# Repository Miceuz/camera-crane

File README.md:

# camera-crane
Electronics of camera crane for stop motion animation

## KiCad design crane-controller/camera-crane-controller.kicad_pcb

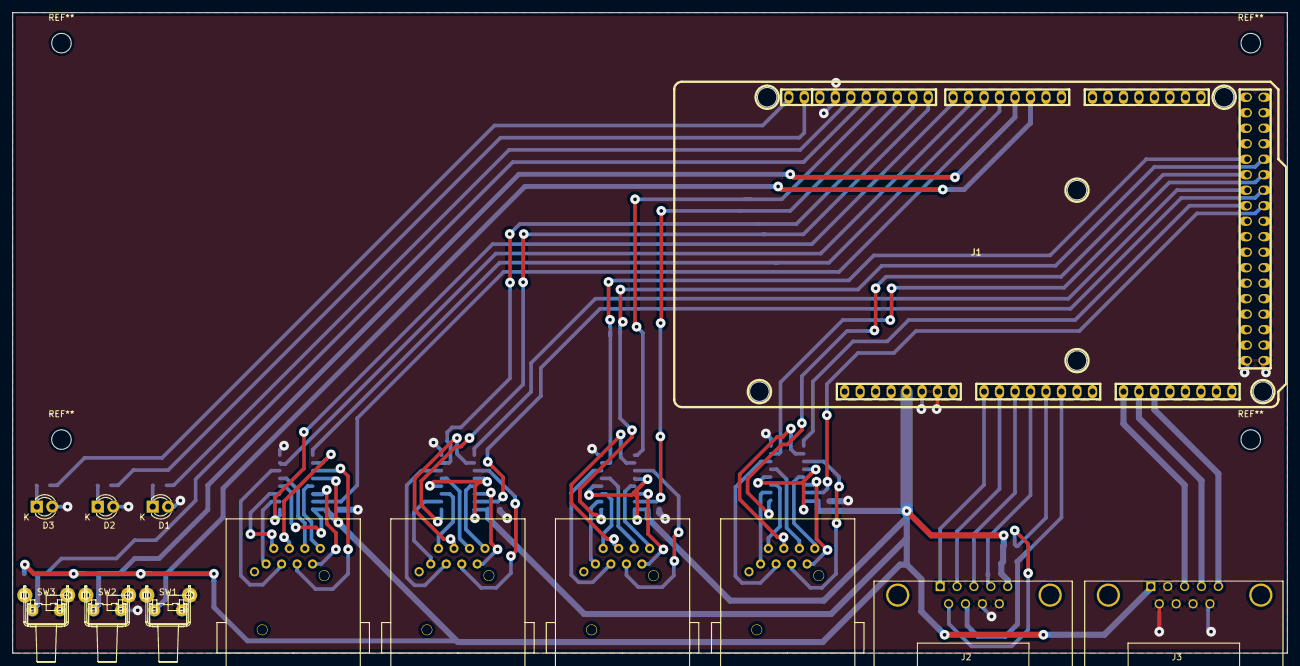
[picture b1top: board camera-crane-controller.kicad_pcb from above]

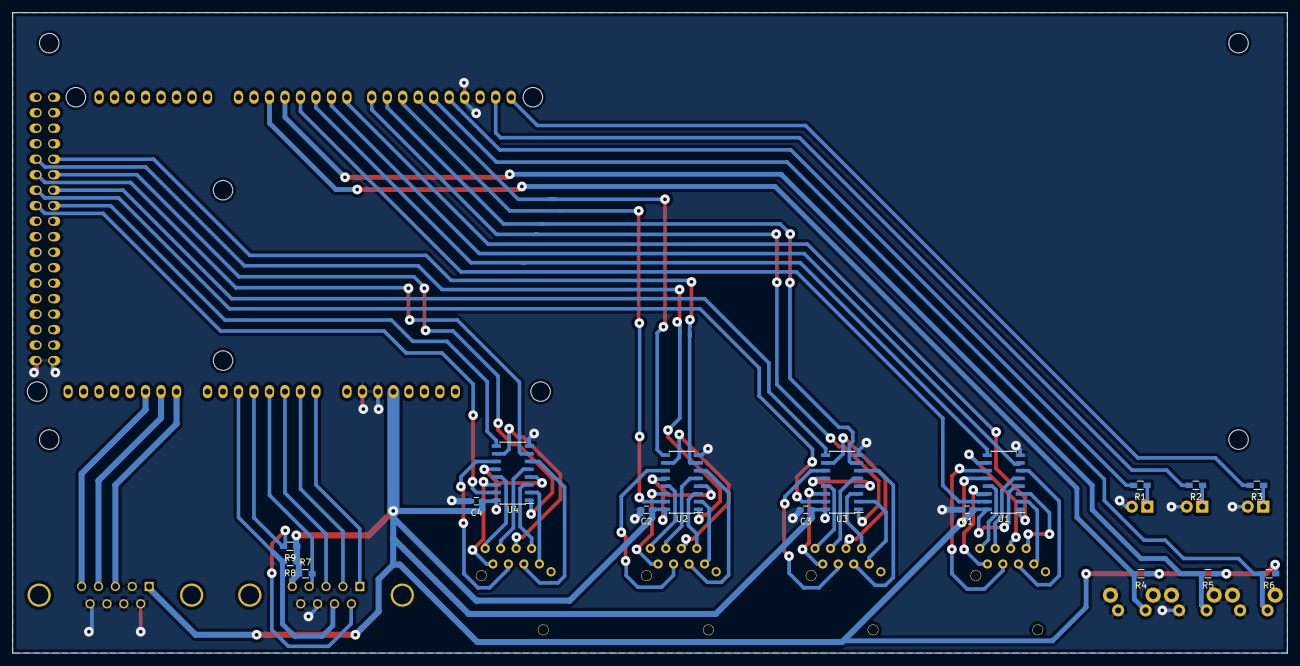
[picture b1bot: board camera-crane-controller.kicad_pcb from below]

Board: 2 copper layers, 209.0 x 105.0 mm, 30 parts (17 on the bottom side), 68 nets.

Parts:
C1, C2, C3, C4: C; C_0603_HandSoldering
D1, D2, D3: LED; LED-3MM
J1: Arduino_Mega_Header; arduino_mega_header
J2: DB9; 182-009-113
J3: DB9; DB9MC
P1, P2, P3, P4: CONN_01X08; NE8FAH
R1, R2, R3, R4, R5, R6: R; R_0603_HandSoldering
R7, R8, R9: 1k; R_0603_HandSoldering
SW1, SW2, SW3: SW_PUSH; SKHHLR
U1, U2, U3, U4: MAX3040; SOIC-16_3.9x9.9mm_Pitch1.27mm

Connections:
/DIR_AUX1: J1.54, U3.15
/DIR_AUX2: J1.53, U4.15
/DIR_FOCUS: J1.55, U4.7
/DIR_PAN: J1.80, U2.9
/DIR_TILT: J1.56, U2.1
/DIR_X: J1.74, U1.9
/DIR_Y: J1.76, U1.1
/DIR_Z: J1.78, U3.7
/END_SW1: J1.17, J3.3
/END_SW2: J1.18, J3.4
/END_SW3: J1.19, J3.5
/JOY_BUTTON_BOT: J1.13, J2.6, R9.2
/JOY_BUTTON_DEADMAN: J1.12, J2.4, R7.2
/JOY_BUTTON_TOP: J1.14, J2.7, R8.2
/JOY_REF: J1.9, J2.1
/JOY_X: J1.10, J2.2
/JOY_Y: J1.11, J2.3
/LED1: J1.82, R1.2
/LED2: J1.85, R2.2
/LED3: J1.86, R3.2
/STEP_AUX1: J1.36, U3.9
/STEP_AUX2: J1.35, U4.9
/STEP_FOCUS: J1.37, U4.1
/STEP_PAN: J1.79, U2.15
/STEP_TILT: J1.38, U2.7
/STEP_X: J1.73, U1.15
/STEP_Y: J1.75, U1.7
/STEP_Z: J1.77, U3.1
/SW1: J1.71, R4.2, SW1.1
/SW2: J1.72, R5.2, SW2.1
/SW3: J1.81, R6.2, SW3.1
GND: C1.2, C2.2, C3.2, C4.2, D1.2, D2.2, D3.2, J1.6, J1.7, J1.25, J1.43, J1.83, J2.8, J2.9, J3.2, J3.6, J3.7, J3.8, J3.9, SW1.2, SW1.G, SW2.2, SW2.G, SW3.2, SW3.G, U1.8, U2.8, U3.8, U4.8
unnamed: D1.1, R1.1
unnamed: D2.1, R2.1
unnamed: D3.1, R3.1
unnamed: P1.1, U1.2
unnamed: P1.2, U1.3
unnamed: P1.3, U1.6
unnamed: P1.4, U1.10
unnamed: P1.5, U1.11
unnamed: P1.6, U1.5
unnamed: P1.7, U1.14
unnamed: P1.8, U1.13
unnamed: P2.1, U3.2
unnamed: P2.2, U3.3
unnamed: P2.3, U3.6
unnamed: P2.4, U3.10
unnamed: P2.5, U3.11
unnamed: P2.6, U3.5
unnamed: P2.7, U3.14
unnamed: P2.8, U3.13
unnamed: P3.1, U2.2
unnamed: P3.2, U2.3
unnamed: P3.3, U2.6
unnamed: P3.4, U2.10
unnamed: P3.5, U2.11
unnamed: P3.6, U2.5
unnamed: P3.7, U2.14
unnamed: P3.8, U2.13
unnamed: P4.1, U4.2
unnamed: P4.2, U4.3
unnamed: P4.3, U4.6
unnamed: P4.4, U4.10
unnamed: P4.5, U4.11
unnamed: P4.6, U4.5
unnamed: P4.7, U4.14
unnamed: P4.8, U4.13
VCC: C1.1, C2.1, C3.1, C4.1, J1.5, J1.42, J1.60, J2.5, J3.1, R4.1, R5.1, R6.1, R7.1, R8.1, R9.1, U1.4, U1.12, U1.16, U2.4, U2.12, U2.16, U3.4, U3.12, U3.16, U4.4, U4.12, U4.16

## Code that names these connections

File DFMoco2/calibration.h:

#include "common.h"
#include <Bounce2.h>

#define baseForward()     digitalWrite(DIR_BASE, LOW)
#define baseReverse()     digitalWrite(DIR_BASE, HIGH)
#define panForward()      digitalWrite(DIR_PAN, HIGH)
#define panReverse()      digitalWrite(DIR_PAN, LOW)
#define tiltForward()      digitalWrite(DIR_TILT, HIGH)
#define tiltReverse()      digitalWrite(DIR_TILT, LOW)

#define LED1 13
#define LED2 20
#define LED3 21

#define SW1 2
#define SW2 3
#define SW3 12

#define END_SW1 A8
#define END_SW2 A9
#define END_SW3 A10

Bounce sw1 = Bounce(SW1, 10);
Bounce sw2 = Bounce(SW2, 10);
Bounce sw3 = Bounce(SW3, 10);

Bounce esw1 = Bounce(END_SW1, 10);
Bounce esw2 = Bounce(END_SW2, 10);
Bounce esw3 = Bounce(END_SW3, 10);

uint32_t stepTs;
uint16_t pulseUs = 4000;

uint32_t steps = 0;
uint8_t phase = HIGH;

void calibrateSetup() {
  pinMode(LED1, OUTPUT);
  pinMode(LED2, OUTPUT);
  pinMode(LED3, OUTPUT);

  digitalWrite(LED1, HIGH);
  digitalWrite(LED2, HIGH);
  digitalWrite(LED3, HIGH);
  delay(2000);
  digitalWrite(LED1, LOW);
  digitalWrite(LED2, LOW);
  digitalWrite(LED3, LOW);
}

void move(uint8_t stepPin, uint32_t stepsToDo, uint8_t waitForSwitch) {
  steps = 0;
  while(steps < stepsToDo) {
    if(isPulseTime(stepTs, pulseUs)) {
      digitalWrite(stepPin, phase);
      phase = !phase;
      steps++;
      stepTs = micros();

      esw1.update();
      esw2.update();
      esw3.update();

      if(esw1.read()) {
        if(waitForSwitch && STEP_BASE == stepPin) {
          break;
        }
      }

      if(esw2.read()) {
        if(waitForSwitch && STEP_PAN == stepPin) {
          break;
        }
      }

      if(esw3.read()) {
        if(waitForSwitch && STEP_TILT == stepPin) {
          break;
        }
      }
    }
  }
  Serial.println(String("Done ") + steps + String(" out of ") + stepsToDo);
}

uint8_t touchBase() {
  digitalWrite(LED3, LOW);
  digitalWrite(LED2, HIGH);

  pulseUs = 500;
  baseForward();
  move(STEP_BASE, 10000, 1);
  if(steps == 10000) {
    digitalWrite(LED3, HIGH);
    return 0;
  }
  delay(2000);

  pulseUs = 1000;
  baseReverse();
  move(STEP_BASE, 1000, 0);

  delay(2000);
  
  pulseUs = 8000;
  baseForward();
  move(STEP_BASE, 2000, 1);

  delay(2000);

  baseReverse();

  steps=0;
  while(esw1.read()) {
    if(isPulseTime(stepTs, pulseUs)) {
      digitalWrite(STEP_BASE, phase);
      phase = !phase;
      steps++;
      stepTs = micros();
    }
    esw1.update();
  }

  Serial.println(String("BASE backlash ") + steps);

  move(STEP_BASE, 4000, 0);
  digitalWrite(LED2, LOW);
  return 1;
}

uint8_t touchPan() {
  digitalWrite(LED3, LOW);
  digitalWrite(LED2, HIGH);

  pulseUs = 2000;
  panForward();
  move(STEP_PAN, 10000, 1);

  if(10000 == steps) {
    digitalWrite(LED3, HIGH);
    return 0;
  }
  
  delay(3000);

  panReverse();
  pulseUs = 750;
  move(STEP_PAN, 30000, 0);

  delay(5000);

  panForward();
  move(STEP_PAN, 32000, 1);
  delay(5000);

  pulseUs = 2000;
  panReverse();
  steps=0;
  while(esw2.read()) {
    if(isPulseTime(stepTs, pulseUs)) {
      digitalWrite(STEP_PAN, phase);
      phase = !phase;
      steps++;
      stepTs = micros();
    }
    esw2.update();
  }

  Serial.println(String("PAN backlash ") + steps);

  move(STEP_PAN, 1800, 0);

  digitalWrite(LED2, LOW);
  return 1;
}

uint8_t touchTilt() {
  digitalWrite(LED3, LOW);
  digitalWrite(LED2, HIGH);

  pulseUs = 2000;
  tiltForward();
  move(STEP_TILT, 10000, 1);

  if(10000 == steps) {
    digitalWrite(LED3, HIGH);
    return 0;
  }
  delay(2000);

  pulseUs = 8000;
  tiltReverse();
  move(STEP_TILT, 500, 0);
  delay(2000);

  tiltForward();

  move(STEP_TILT, 1000, 1);
  delay(2000);

  tiltReverse();
  steps=0;
  while(esw3.read()) {
    if(isPulseTime(stepTs, pulseUs)) {
      digitalWrite(STEP_TILT, phase);
      phase = !phase;
      steps++;
      stepTs = micros();
    }
    esw3.update();
  }

  Serial.println(String("TILT backlash ") + steps);

  move(STEP_TILT, 5000, 1);

  return 1;
}

void calibrate() {
  Serial.println("Starting calibration...");
  uint32_t startTs = millis();

  if(touchBase() && touchTilt() && touchPan()){ 
    baseReverse();
    pulseUs = 1000;
    move(STEP_BASE, 100000, 0);

    Serial.println(String("Calibration took ") + (millis() - startTs) + String("ms"));
    for(int i = 0; i < 5; i++) {
      digitalWrite(LED1, HIGH);
      delay(500);
      digitalWrite(LED1, LOW);
      delay(500);
    }
  }
}

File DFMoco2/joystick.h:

#include "common.h"
#include <Bounce2.h>

#define JOY_BUTTON_DEADMAN A3
#define JOY_BUTTON_TOP A5
#define JOY_BUTTON_BOT A4
#define JOY_REF A0
#define JOY_Y A1
#define JOY_X A2

#define JOY_READ_PERIOD_MS 100

#define PIN_NONE 0

#define JOY_SLOW_THRESHOLD 350

Bounce joystickDeadman = Bounce(JOY_BUTTON_DEADMAN, 10);

int16_t joystickRef;
int16_t joystickY;
int16_t joystickX;

uint16_t pulseUsY;
uint16_t pulseUsX;

uint16_t curPulseUsY;
uint16_t curPulseUsX;

uint32_t lastJoyRead;

uint32_t stepYts;
uint32_t stepXts;


int stepYPin = PIN_NONE;
int stepXPin = PIN_NONE;

uint16_t maxPulseLengthY = 4000;
uint16_t maxPulseLengthX = 4000;

uint8_t phaseY = 0;
uint8_t phaseX = 0;

uint32_t accelerationTs = 0;


inline static uint8_t isAccelerationTime(uint32_t accTs) {
  return micros() - accTs > 200;
}

void joystickSetup() {
}

inline static void setYDirection() {
	if(joystickY > 0) {
		digitalWrite(DIR_TILT, HIGH);
		digitalWrite(DIR_BASE, LOW);      
		digitalWrite(DIR_HEAD_TILT, HIGH);
	} else {
		digitalWrite(DIR_TILT, LOW);
		digitalWrite(DIR_BASE, HIGH);
		digitalWrite(DIR_HEAD_TILT, LOW);
	}
}

inline static void setXDirection() {
	if(joystickX > 0) {
		digitalWrite(DIR_PAN, HIGH);
		digitalWrite(DIR_HEAD_PAN, LOW);
	} else {
		digitalWrite(DIR_PAN, LOW);
		digitalWrite(DIR_HEAD_PAN, HIGH);
	}
}

void setMaxPulseLength(int16_t joystickVal, uint16_t *maxPulseLength, uint16_t slow, uint16_t fast) {
	if(abs(joystickVal) < JOY_SLOW_THRESHOLD) {
		*maxPulseLength = slow;
	} else {
		*maxPulseLength = fast;
	}
}

inline static void setupYMovement() {
	if(LOW == digitalRead(JOY_BUTTON_TOP)) {
		stepYPin = STEP_TILT;
		setMaxPulseLength(joystickY, &maxPulseLengthY, 400, 100);

		if(stepYPin == PIN_NONE) {
			curPulseUsY = 400;
		}
	} else if(LOW == digitalRead(JOY_BUTTON_BOT)) {
		stepYPin = STEP_BASE;
		setMaxPulseLength(joystickY, &maxPulseLengthY, 4000, 300);
	} else {
		stepYPin = STEP_HEAD_TILT;
		setMaxPulseLength(joystickY, &maxPulseLengthY, 4000, 1000);
	}

	pulseUsY = maxPulseLengthY - map(abs(joystickY), 0, 1023 - joystickRef, 0, maxPulseLengthY);

	if(pulseUsY > 65000) {
		pulseUsY = 20;
	}
}

inline static void setupXMovement() {
	if(LOW == digitalRead(JOY_BUTTON_TOP)) {
		stepXPin = STEP_PAN;
		setMaxPulseLength(joystickX, &maxPulseLengthX, 1500, 400);
	} else {
		stepXPin = STEP_HEAD_PAN;
		setMaxPulseLength(joystickX, &maxPulseLengthX, 4000, 1000);
	}
	pulseUsX = maxPulseLengthX - map(abs(joystickX), 0, 1023 - joystickRef, 0, maxPulseLengthX); 
}

inline static void joystickRead() {
	joystickRef = analogRead(JOY_REF);
	joystickY = analogRead(JOY_Y) - joystickRef;
	joystickX = analogRead(JOY_X) - joystickRef;

	Serial.print(joystickX);
	Serial.print(" ");
	Serial.print(joystickY);

	if(abs(joystickY) > 20) {
		setYDirection();
		setupYMovement();
	} else {
		stepYPin = PIN_NONE;
		curPulseUsY = 4000;
	}

	if(abs(joystickX) > 20) {
		setXDirection();
		setupXMovement();
	} else {
		stepXPin = PIN_NONE;
		curPulseUsX = 4000;
	}

	Serial.print(" ");
	Serial.print(curPulseUsX);
	Serial.print(" ");
	Serial.print(curPulseUsY);
	Serial.print(" ");
	Serial.print(maxPulseLengthX);
	Serial.print(" ");
	Serial.print(maxPulseLengthY);
	Serial.println();
}

uint8_t isTimeToReadJoystick() {
	return millis() - lastJoyRead > JOY_READ_PERIOD_MS;
}

void processJoystick() {
	if(isTimeToReadJoystick()) {
		joystickRead();
		lastJoyRead = millis();
	}
  
	if(PIN_NONE != stepYPin) {
    	if(isPulseTime(stepYts, curPulseUsY)) {
      		digitalWrite(stepYPin, phaseY);
      		phaseY = !phaseY;
      		stepYts = micros();
    	}
    
	    if(isAccelerationTime(accelerationTs)){
			if(curPulseUsY < pulseUsY) {
				curPulseUsY +=1;
			} else if(curPulseUsY > pulseUsY) {
				curPulseUsY -=1;
			}
			accelerationTs = micros();
	    }
	}

	if(PIN_NONE != stepXPin) {
		if(isPulseTime(stepXts, curPulseUsX)) {
			digitalWrite(stepXPin, phaseX);
			phaseX = !phaseX;
			stepXts = micros();
		}

		if(isAccelerationTime(accelerationTs)){
			if(curPulseUsX < pulseUsX) {
				curPulseUsX +=1;
			} else if(curPulseUsX > pulseUsX) {
				curPulseUsX -=1;
			}
			accelerationTs = micros();
		}

	}
}

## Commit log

2016-07-18 Initial commit. Postfactum. Board ordered and done
2016-07-30 Add the latest MOCO code
2016-07-30 Add some photos
2016-07-30 Unimportant text move
2016-08-01 Less pan turn at the end of calibration, move base away after calibration is done
